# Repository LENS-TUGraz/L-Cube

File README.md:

# L-Cube Repository

This repository contains the source code for L-CUBE, a low-cost and easy-to-setup localization system with the Lighthouse base stations. The L-Cube consists of five tiles, which can be used in standalone mode via a serial cable connection, or be aggregated in a cube that can interact with other systems via MQTT or serial connection.

In order to build and setup L-CUBE, the hardware folder contains all components for manufacturing, whereas the README from the src folder provides further information about how to use the software.

### Folder structure

| **Folder** | **Description** |
|---|---|
| assets | Metadata |
| hardware | Informations to build your own hardware |
| src | Arduino (c++) sources for the tiles and cube controller |
| tools | Python tools/scripts to interact with the tiles and cubes |

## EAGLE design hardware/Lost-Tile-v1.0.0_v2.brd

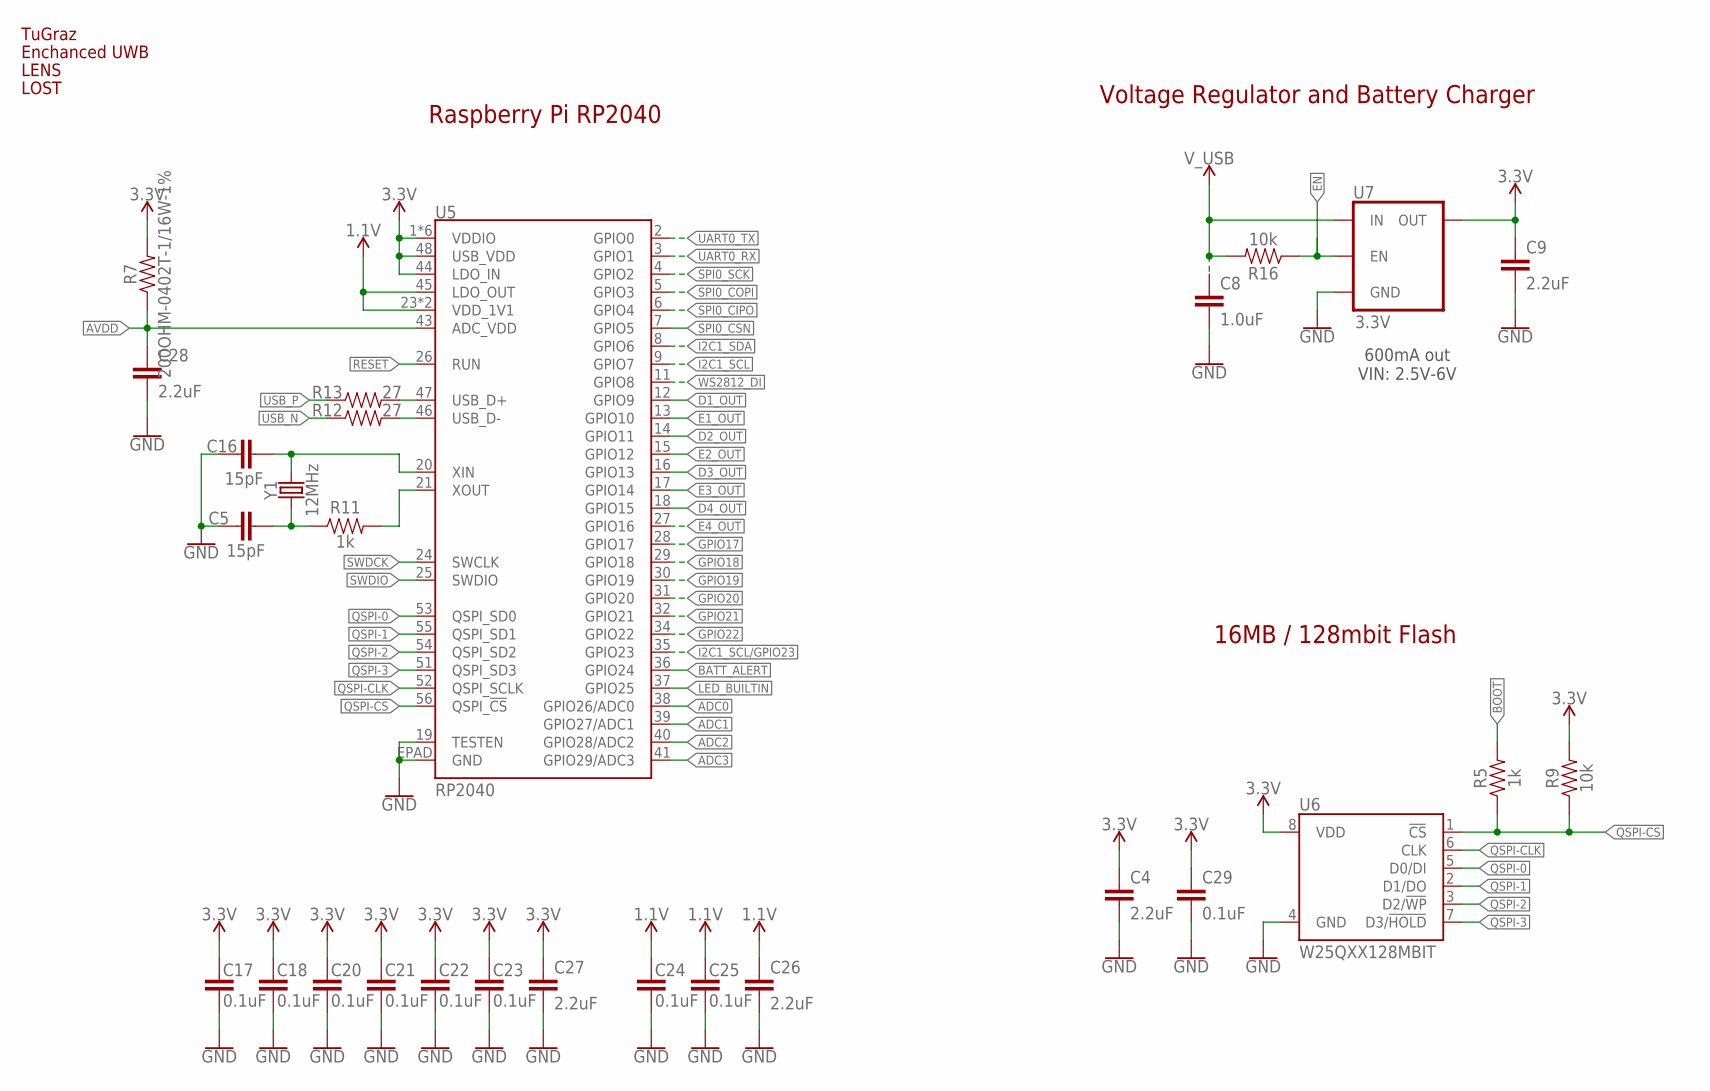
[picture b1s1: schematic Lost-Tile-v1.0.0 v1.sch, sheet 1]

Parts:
C4, C9, C26, C27, C28: 2.2uF; 0402-TIGHT
C5, C16: 15pF; 0402-TIGHT
C8: 1.0uF; 0402-TIGHT
C17, C18, C20, C21, C22, C23, C24, C25, C29: 0.1uF; 0402-TIGHT
LG1: TU-LOGOSMALL-BICOL; TU-LOGO-SMALL-BICOL
LG2: EUWBBICOL; EUWB_LOGO-BICOL
LG3: LENS
LG4: LOST_LOGO
R5, R11: 1k; 0402-TIGHT
R7: 200OHM-0402T-1/16W-1%; 0402-TIGHT
R9, R16: 10k; 0402-TIGHT
R12, R13: 27; 0402-TIGHT
U5: RP2040; QFN-56
U6: W25QXX128MBIT; WSON-8-6X5-SKINNY_CENTERPAD
U7: 3.3V; SOT23-5
Y1: 12MHz; CRYSTAL-SMD-2X2.5MM

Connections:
1.1V: C24.1, C25.1, C26.1, U5.23 (VDD_1V1), U5.45 (LDO_OUT), U5.50 (VDD_1V1)
3.3V: C4.1, C9.1, C17.1, C18.1, C20.1, C21.1, C22.1, C23.1, C27.1, C29.1, R7.2, R9.2, U5.1 (VDDIO), U5.10 (VDDIO), U5.22 (VDDIO), U5.33 (VDDIO), U5.42 (VDDIO), U5.44 (LDO_IN), U5.48 (USB_VDD), U5.49 (VDDIO), U6.8 (VDD), U7.5 (OUT); also elsewhere on the board
!RESET!: U5.26 (RUN); also elsewhere on the board
ADC0: U5.38 (GPIO26/ADC0)
ADC1: U5.39 (GPIO27/ADC1)
ADC2: U5.40 (GPIO28/ADC2)
ADC3: U5.41 (GPIO29/ADC3)
AVDD: C28.1, R7.1, U5.43 (ADC_VDD)
BATT_ALERT: U5.36 (GPIO24)
BOOT: R5.2; also elsewhere on the board
D1_OUT: U5.12 (GPIO9); also elsewhere on the board
D2_OUT: U5.14 (GPIO11); also elsewhere on the board
D3_OUT: U5.16 (GPIO13); also elsewhere on the board
D4_OUT: U5.18 (GPIO15); also elsewhere on the board
E1_OUT: U5.13 (GPIO10); also elsewhere on the board
E2_OUT: U5.15 (GPIO12); also elsewhere on the board
E3_OUT: U5.17 (GPIO14); also elsewhere on the board
E4_OUT: U5.27 (GPIO16); also elsewhere on the board
EN: R16.1, U7.3 (EN)
GND: C4.2, C5.1, C8.2, C9.2, C16.1, C17.2, C18.2, C20.2, C21.2, C22.2, C23.2, C24.2, C25.2, C26.2, C27.2, C28.2, C29.2, U5.19 (TESTEN), U5.EPAD (GND), U6.4 (GND), U7.2 (GND); also elsewhere on the board
GPIO17: U5.28 (GPIO17)
GPIO18: U5.29 (GPIO18)
GPIO19: U5.30 (GPIO19)
GPIO20: U5.31 (GPIO20); also elsewhere on the board
GPIO21: U5.32 (GPIO21); also elsewhere on the board
GPIO22: U5.34 (GPIO22); also elsewhere on the board
I2C1_SCL: U5.9 (GPIO7); also elsewhere on the board
I2C1_SCL/GPIO23: U5.35 (GPIO23)
I2C1_SDA: U5.8 (GPIO6); also elsewhere on the board
LED_BUILTIN: U5.37 (GPIO25); also elsewhere on the board
unnamed: R11.2, U5.21 (XOUT)
unnamed: C16.2, U5.20 (XIN), Y1.P3 (2)
unnamed: C5.2, R11.1, Y1.P1 (1)
QSPI-0: U5.53 (QSPI_SD0), U6.5 (D0/DI)
QSPI-1: U5.55 (QSPI_SD1), U6.2 (D1/DO)
QSPI-2: U5.54 (QSPI_SD2), U6.3 (D2/!WP!)
QSPI-3: U5.51 (QSPI_SD3), U6.7 (D3/!HOLD!)
QSPI-CLK: U5.52 (QSPI_SCLK), U6.6 (CLK)
QSPI-CS: R5.1, R9.1, U5.56 (QSPI_!CS!), U6.1 (!CS!)
SPI0_CIPO: U5.6 (GPIO4); also elsewhere on the board
SPI0_COPI: U5.5 (GPIO3); also elsewhere on the board
SPI0_CSN: U5.7 (GPIO5); also elsewhere on the board
SPI0_SCK: U5.4 (GPIO2); also elsewhere on the board
SWDCK: U5.24 (SWCLK)
SWDIO: U5.25 (SWDIO)
UART0_RX: U5.3 (GPIO1); also elsewhere on the board
UART0_TX: U5.2 (GPIO0); also elsewhere on the board
USB_F_N: R12.2, U5.46 (USB_D-)
USB_F_P: R13.2, U5.47 (USB_D+)
USB_N: R12.1; also elsewhere on the board
USB_P: R13.1; also elsewhere on the board
V_USB: C8.1, R16.2, U7.1 (IN); also elsewhere on the board
WS2812_DI: U5.11 (GPIO8); also elsewhere on the board

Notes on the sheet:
Raspberry Pi RP2040
16MB / 128mbit Flash
Voltage Regulator and Battery Charger
600mA out VIN: 2.5V-6V

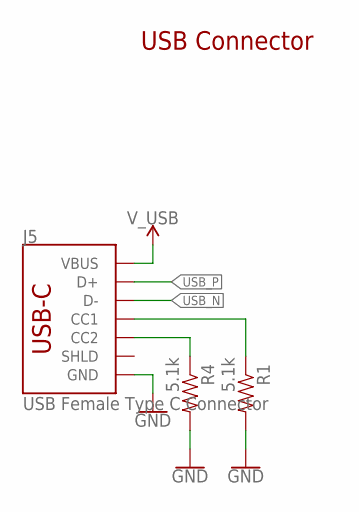
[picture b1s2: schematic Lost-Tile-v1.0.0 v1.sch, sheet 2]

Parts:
J5: USB Female Type C Connector; USB-C-16P-4LAYER-ISOLATED
R1, R4: 5.1k; 0402-TIGHT

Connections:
GND: J5.GND, J5.GND2 (GND), R1.2, R4.2; also elsewhere on the board
unnamed: J5.A5 (CC1), R1.1
unnamed: J5.B5 (CC2), R4.1
USB_N: J5.A7 (D-), J5.B7 (D-); also elsewhere on the board
USB_P: J5.A6 (D+), J5.B6 (D+); also elsewhere on the board
V_USB: J5.VBUS1 (VBUS), J5.VBUS2 (VBUS); also elsewhere on the board

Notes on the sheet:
USB Connector

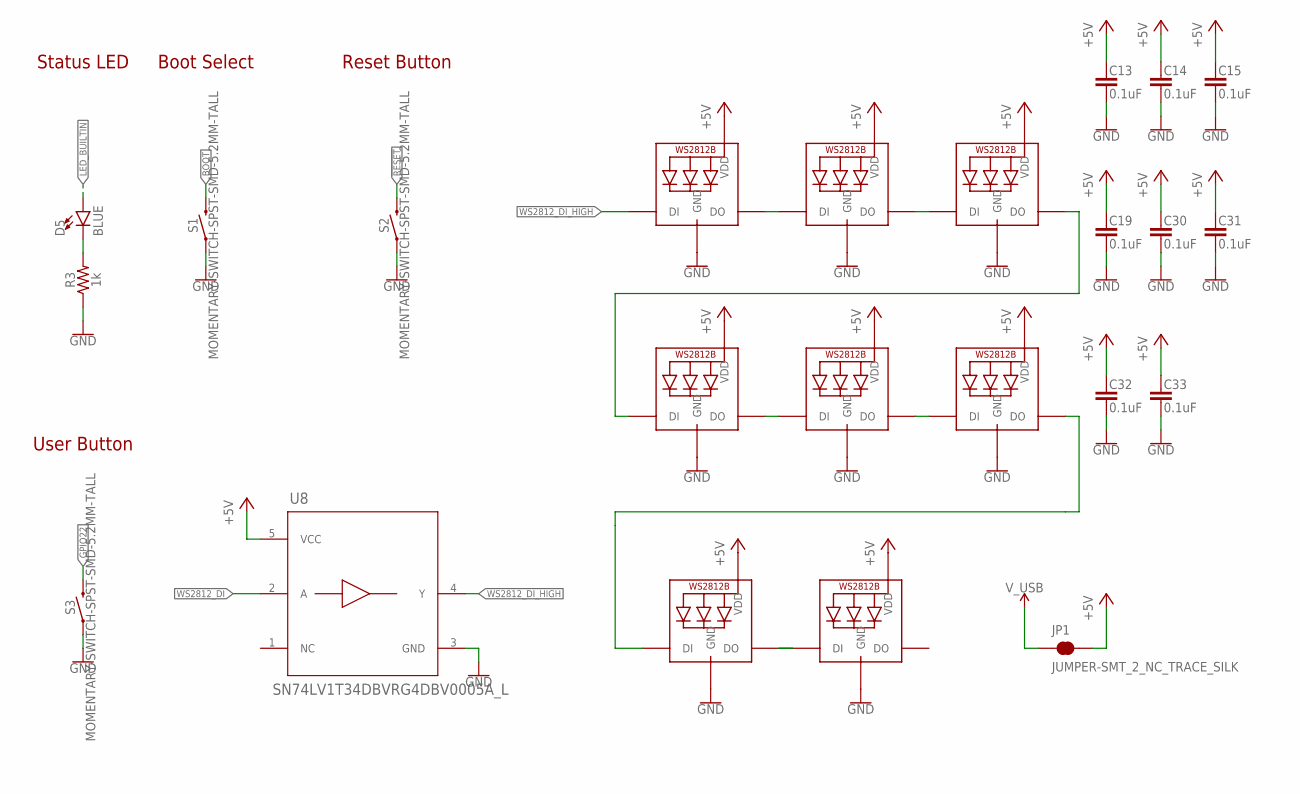
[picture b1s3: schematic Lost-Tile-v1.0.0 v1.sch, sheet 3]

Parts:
C13, C14, C15, C19, C30, C31, C32, C33: 0.1uF; 0402-TIGHT
D5: BLUE; LED-0603
JP1: JUMPER-SMT_2_NC_TRACE_SILK; SMT-JUMPER_2_NC_TRACE_SILK
LED1, LED2, LED3, LED4, LED5, LED6, LED7, LED8: WS2812B5050; WS2812B
R3: 1k; 0402-TIGHT
S1, S2, S3: MOMENTARY-SWITCH-SPST-SMD-5.2MM-TALL; TACTILE_SWITCH_SMD_5.2MM
U8: SN74LV1T34DBVRG4DBV0005A_L; DBV0005A_L

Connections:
!RESET!: S2.3 (2); also elsewhere on the board
+5V: C13.1, C14.1, C15.1, C19.1, C30.1, C31.1, C32.1, C33.1, JP1.2, LED1.1-VDD (VDD), LED2.1-VDD (VDD), LED3.1-VDD (VDD), LED4.1-VDD (VDD), LED5.1-VDD (VDD), LED6.1-VDD (VDD), LED7.1-VDD (VDD), LED8.1-VDD (VDD), U8.5 (VCC); also elsewhere on the board
BOOT: S1.3 (2); also elsewhere on the board
GND: C13.2, C14.2, C15.2, C19.2, C30.2, C31.2, C32.2, C33.2, LED1.3-GND (GND), LED2.3-GND (GND), LED3.3-GND (GND), LED4.3-GND (GND), LED5.3-GND (GND), LED6.3-GND (GND), LED7.3-GND (GND), LED8.3-GND (GND), R3.1, S1.1, S2.1, S3.1, U8.3 (GND); also elsewhere on the board
GPIO22: S3.3 (2); also elsewhere on the board
LED_BUILTIN: D5.A; also elsewhere on the board
unnamed: D5.C, R3.2
unnamed: LED1.2-DOUT (DO), LED2.4-DIN (DI)
unnamed: LED2.2-DOUT (DO), LED3.4-DIN (DI)
unnamed: LED6.2-DOUT (DO), LED7.4-DIN (DI)
unnamed: LED3.2-DOUT (DO), LED4.4-DIN (DI)
unnamed: LED7.2-DOUT (DO), LED8.4-DIN (DI)
unnamed: LED4.2-DOUT (DO), LED5.4-DIN (DI)
unnamed: LED5.2-DOUT (DO), LED6.4-DIN (DI)
V_USB: JP1.1; also elsewhere on the board
WS2812_DI: U8.2 (A); also elsewhere on the board
WS2812_DI_HIGH: LED1.4-DIN (DI), U8.4 (Y)

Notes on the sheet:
Reset Button
Status LED
Boot Select
User Button

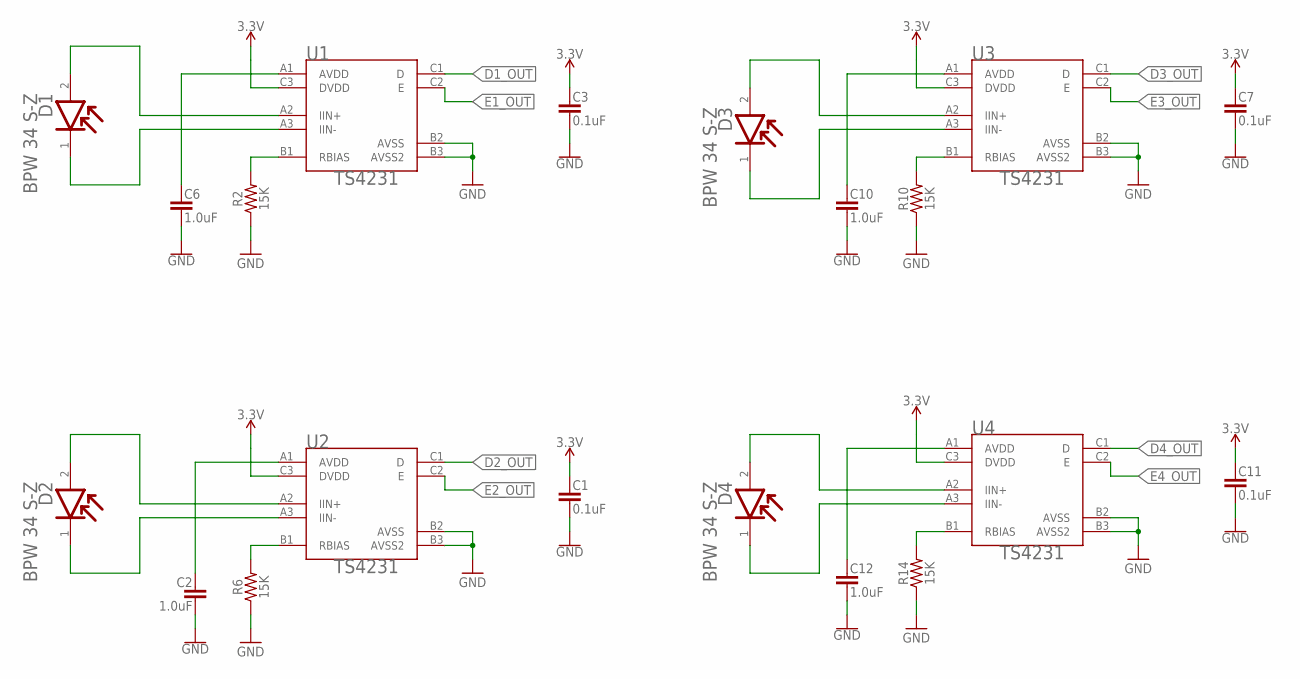
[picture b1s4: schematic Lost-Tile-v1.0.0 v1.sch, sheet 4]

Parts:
C1, C3, C7, C11: 0.1uF; 0402-TIGHT
C2, C6, C10, C12: 1.0uF; 0402-TIGHT
D1, D2, D3, D4: OSRAM_OPTO_SEMICONDUCTORS_INC._BPW_34_S-ZOSRAM_OP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; OSRAM_OPTO_SEMICONDUCTORS_INC._BPW_34_S-Z_0
R2, R6, R10, R14: 15K; 0402-TIGHT
U1, U2, U3, U4: TRIAD_SEMI_TS4231TRIAD_SEMI_TS4231_0_0; TRIAD_SEMI_TS4231_0

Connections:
3.3V: C1.1, C3.1, C7.1, C11.1, U1.C3 (DVDD), U2.C3 (DVDD), U3.C3 (DVDD), U4.C3 (DVDD); also elsewhere on the board
D1_OUT: U1.C1 (D); also elsewhere on the board
D2_OUT: U2.C1 (D); also elsewhere on the board
D3_OUT: U3.C1 (D); also elsewhere on the board
D4_OUT: U4.C1 (D); also elsewhere on the board
E1_OUT: U1.C2 (E); also elsewhere on the board
E2_OUT: U2.C2 (E); also elsewhere on the board
E3_OUT: U3.C2 (E); also elsewhere on the board
E4_OUT: U4.C2 (E); also elsewhere on the board
GND: C1.2, C2.2, C3.2, C6.2, C7.2, C10.2, C11.2, C12.2, R2.1, R6.1, R10.1, R14.1, U1.B2 (AVSS), U1.B3 (AVSS2), U2.B2 (AVSS), U2.B3 (AVSS2), U3.B2 (AVSS), U3.B3 (AVSS2), U4.B2 (AVSS), U4.B3 (AVSS2); also elsewhere on the board
IIN1+: D1.2 (ANODE), U1.A2 (IIN+)
IIN1-: D1.1 (CATHODE), U1.A3 (IIN-)
IIN2+: D2.2 (ANODE), U2.A2 (IIN+)
IIN2-: D2.1 (CATHODE), U2.A3 (IIN-)
IIN3+: D3.2 (ANODE), U3.A2 (IIN+)
IIN3-: D3.1 (CATHODE), U3.A3 (IIN-)
IIN4+: D4.2 (ANODE), U4.A2 (IIN+)
IIN4-: D4.1 (CATHODE), U4.A3 (IIN-)
unnamed: C6.1, U1.A1 (AVDD)
unnamed: C10.1, U3.A1 (AVDD)
unnamed: C2.1, U2.A1 (AVDD)
unnamed: C12.1, U4.A1 (AVDD)
RBIAS: R2.2, U1.B1 (RBIAS)
RBIAS1: R6.2, U2.B1 (RBIAS)
RBIAS2: R10.2, U3.B1 (RBIAS)
RBIAS3: R14.2, U4.B1 (RBIAS)

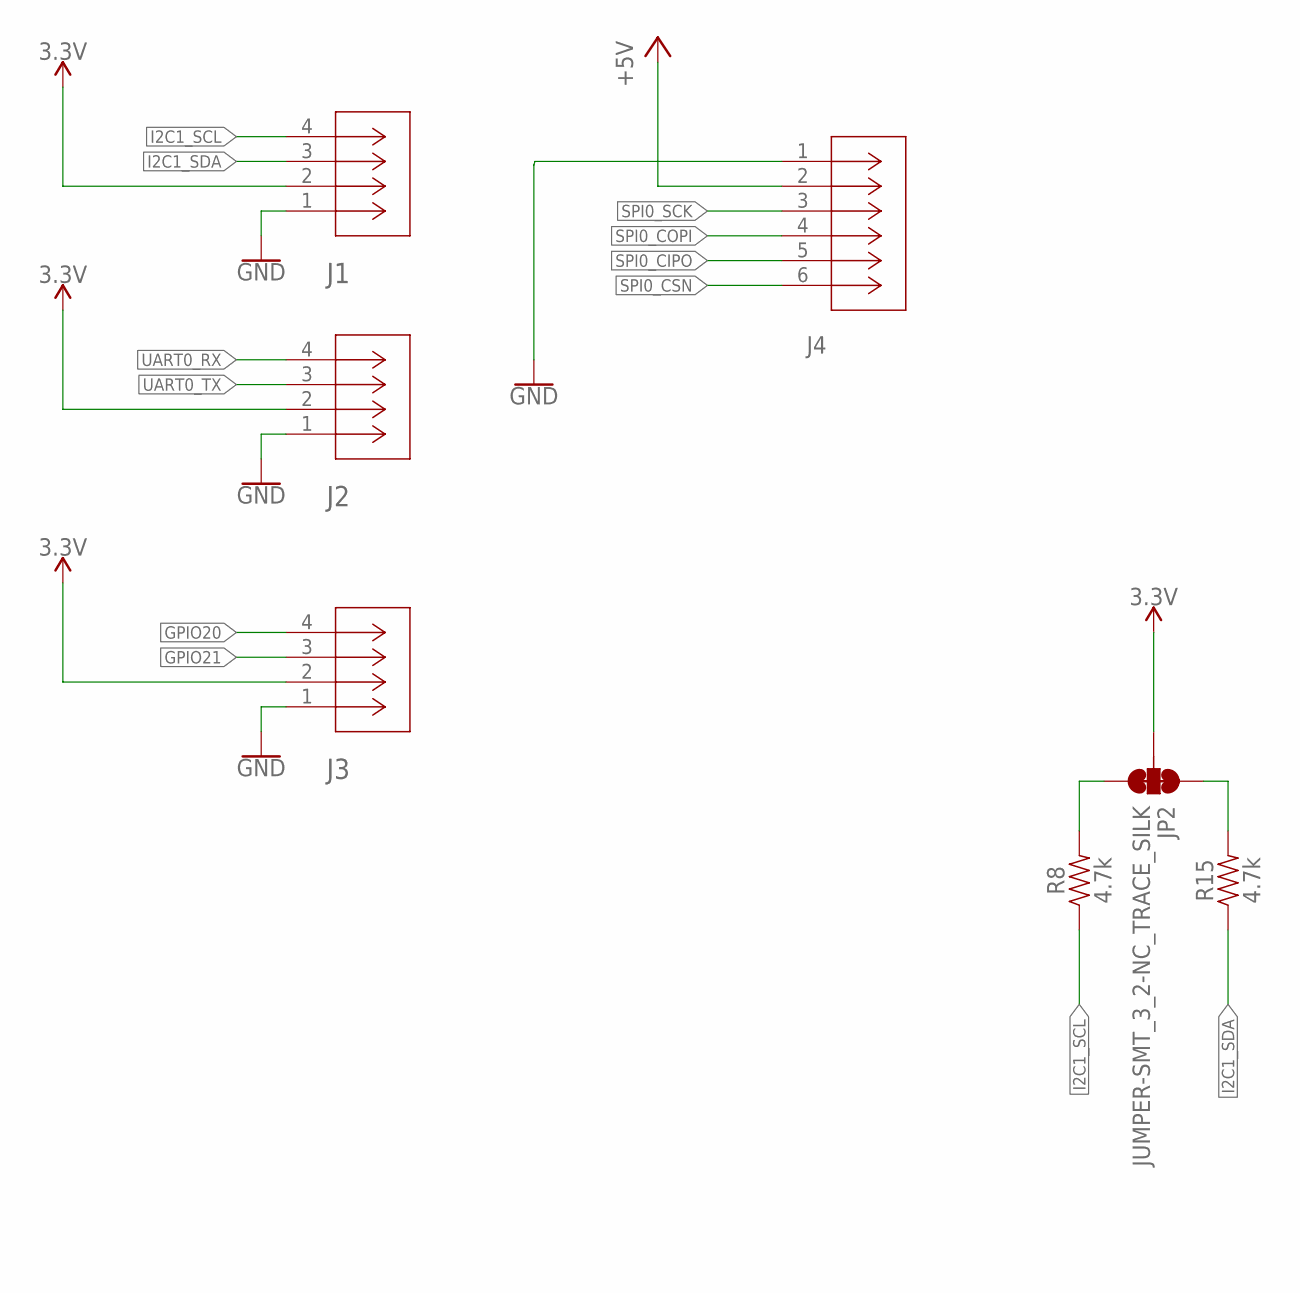
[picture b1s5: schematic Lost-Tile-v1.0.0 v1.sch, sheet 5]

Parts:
J1, J2, J3: BM04B-SRSS-TBT_(LF)(SN)CONN_BM04B-SRSS-TBT_(LF)(S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; CONN_BM04B-SRSS-TBT_(LF)(SN)_J
J4: BM06B-SRSS-TB(LF)(SN)CONN_BM06B-SRSS-TB_JST; CONN_BM06B-SRSS-TB_JST
JP2: JUMPER-SMT_3_2-NC_TRACE_SILK; SMT-JUMPER_3_2-NC_TRACE_SILK
R8, R15: 4.7k; 0402-TIGHT

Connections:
3.3V: J1.2, J2.2, J3.2, JP2.2; also elsewhere on the board
+5V: J4.2; also elsewhere on the board
GND: J1.1, J2.1, J3.1, J4.1; also elsewhere on the board
GPIO20: J3.4; also elsewhere on the board
GPIO21: J3.3; also elsewhere on the board
I2C1_SCL: J1.4, R8.1; also elsewhere on the board
I2C1_SDA: J1.3, R15.1; also elsewhere on the board
unnamed: JP2.3, R8.2
unnamed: JP2.1, R15.2
SPI0_CIPO: J4.5; also elsewhere on the board
SPI0_COPI: J4.4; also elsewhere on the board
SPI0_CSN: J4.6; also elsewhere on the board
SPI0_SCK: J4.3; also elsewhere on the board
UART0_RX: J2.4; also elsewhere on the board
UART0_TX: J2.3; also elsewhere on the board

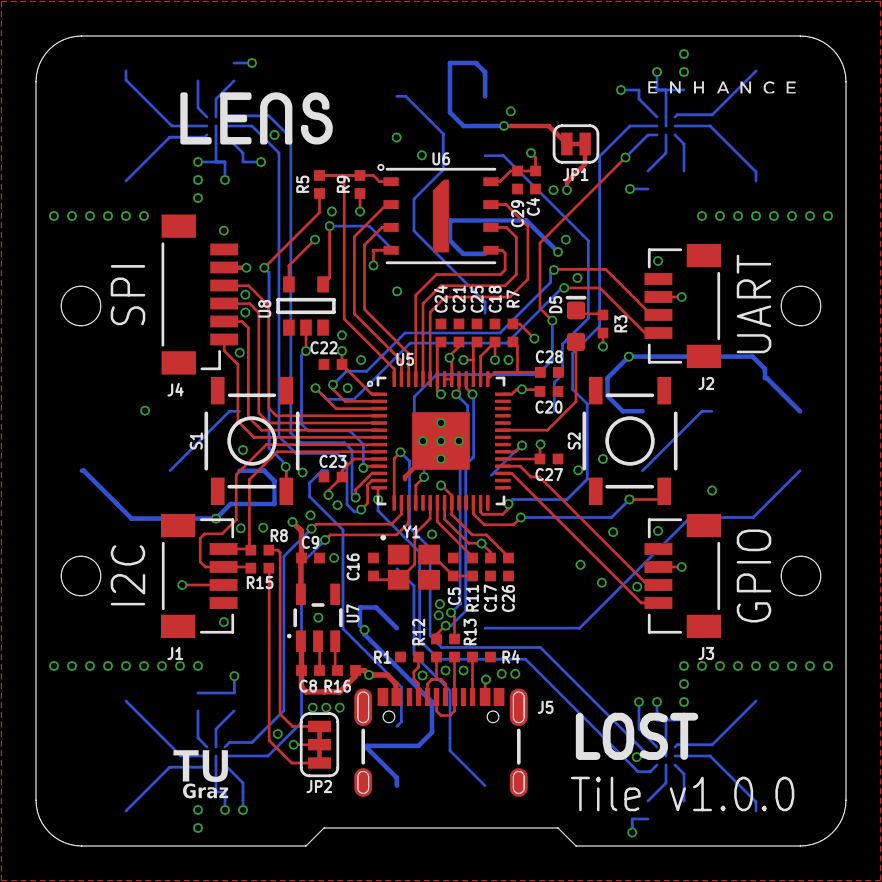
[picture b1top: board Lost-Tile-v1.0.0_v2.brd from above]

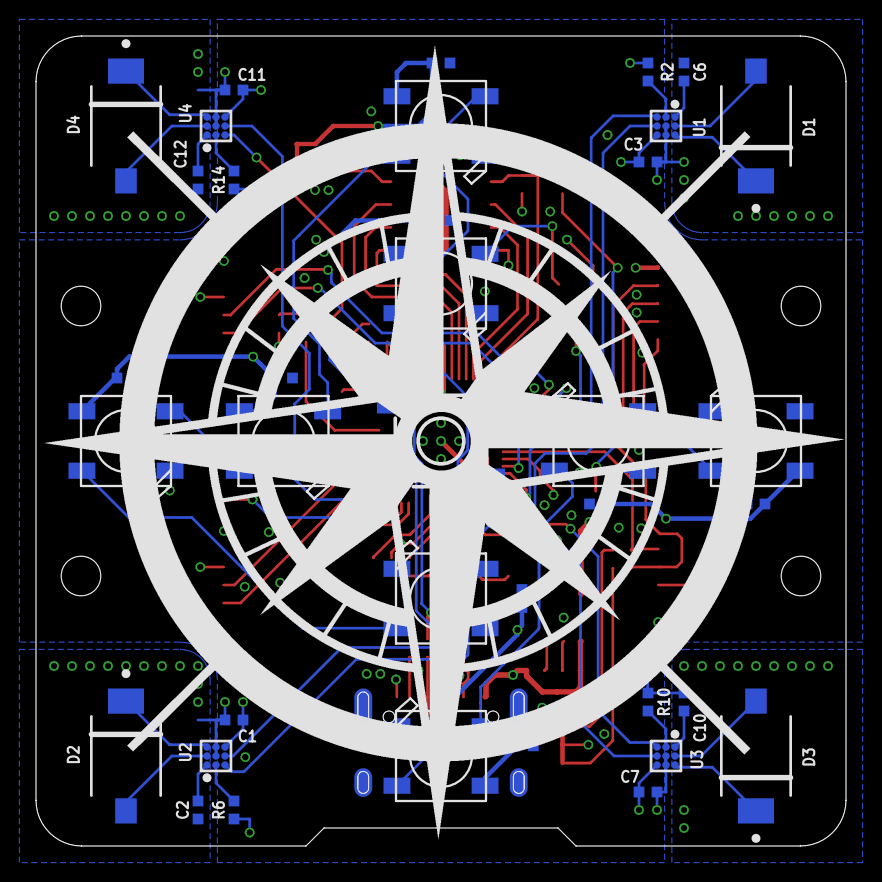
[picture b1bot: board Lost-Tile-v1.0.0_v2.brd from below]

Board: 4 copper layers, 45.0 x 45.0 mm, 85 parts (38 on the bottom side), 72 nets.

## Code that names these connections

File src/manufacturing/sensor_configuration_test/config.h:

/*
 * L-Cube Sensor Configuration Test
 *
 * This program is free software: you can redistribute it and/or modify
 * it under the terms of the GNU General Public License as published by
 * the Free Software Foundation, in version 3.
 *
 * This program is distributed in the hope that it will be useful,
 * but WITHOUT ANY WARRANTY; without even the implied warranty of
 * MERCHANTABILITY or FITNESS FOR A PARTICULAR PURPOSE. See the
 * GNU General Public License for more details.
 *
 * You should have received a copy of the GNU General Public License
 * along with this program. If not, see <http://www.gnu.org/licenses/>.
 *
 */

// change to 0 for actual hardware
#define PROTOTYPE 0

// Divides the brightnes of the leds (2 -> 100%/2 = 50% brightness) (3->33%) (4->25%)
#define DARKNESS_FACTOR 100
#define DF DARKNESS_FACTOR

// wait with test until serial connection to pc is established for dbg messages
#define DBG_SERIAL 1
// for more information about pio and configuration of ts4231
#define DBG_SENSORS 1

#if (PROTOTYPE == 1)
  #define PIN_LEDS 17
  #define D_PINS  3, 0, 26, 28
  #define E_PINS  4, 1, 27, 29
#else
  #define PIN_LEDS 8
  #define D_PINS 15,  9, 11, 13
  #define E_PINS 16, 10, 12, 14
#endif

// leds on top of tile
#define NUM_LEDS 8
// time until next led is set on [ms]
#define DELAY_TIME 500

#define COL_WHITE pixels.Color(255/DF, 255/DF, 255/DF)
#define COL_GREEN pixels.Color(  0/DF, 255/DF,   0/DF)
#define COL_BLUE  pixels.Color(  0/DF,   0/DF, 255/DF)
#define COL_PINK  pixels.Color(255/DF,   0/DF, 255/DF)
#define COL_RED   pixels.Color(255/DF,   0/DF,   0/DF)
#define COL_OFF   pixels.Color(  0/DF,   0/DF,   0/DF)

// number of maximal possible photodiodes
#define MAX_PHOTODIODES 4
// number of photodiodes in use (cannot exceed MAX_PHOTODIODES)
#define NO_PHOTODIODES 4

// highest base station number
#define MAX_BASE_STATIONS 16

// time to receive light once for configuration of ts4231 [ms]
#define LIGHT_TIMEOUT 500

// pins
#define UART_TX  0
#define UART_RX  1
#define SPI_SCK  2
#define SPI_COPI 3
#define SPI_CIPO 4
#define SPI_CSN  5
#define I2C_SDA  6
#define I2C_SCL  7
#define PIN_USERBUTTON 22

// with final tile:
// D4   D1
//
// D2   D3 (connector between D2 and D3)
// connection
// D1 - GPIO9
// E1 - GPIO10
// D2 - GPIO11
// E2 - GPIO12
// D3 - GPIO13
// E3 - GPIO14
// D4 - GPIO15 -> index 0 on software
// E4 - GPIO16 -> index 0 on software
// for software D4 becomes D0, rest stays the same

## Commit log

2024-12-05 initial release

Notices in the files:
parts and their libraries:
SparkFun-Resistors: Licensing: Creative Commons ShareAlike 4.0 International - https://creativecommons.org/licenses/by-sa/4.0
2024-01-04_12-26-39_Library: COPYRIGHT: Copyright (C) 2024 Ultra Librarian. All rights reserved.
